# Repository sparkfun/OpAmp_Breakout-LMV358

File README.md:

SparkFun OpAmp Breakout - LMV358
========================================

[*SparkFun OpAmp Breakout - LMV358 (BOB-09816)*](https://www.sparkfun.com/products/9816)

 This is a simple Op Amp breakout board, set up as a 2-stage amplifier with a gain of 100 (gain of 10 for each stage). 
 The on-board trim pot sets the signal level between the stages, not the feedback path. 
 The bandwidth is set to 15.9kHz by a pair of feedback capacitors, or over 100kHz with the caps removed. 
 The LMV358 opamp can source up to 160mA and works well as a low impedance driver/buffer.

Repository Contents
-------------------

* **/Hardware** - Eagle design files (.brd, .sch)
* **/Production** - Production panel files (.brd)

Documentation
--------------

* **[SparkFun Fritzing repo](https://github.com/sparkfun/Fritzing_Parts)** - Fritzing diagrams for SparkFun products.
* **[SparkFun 3D Model repo](https://github.com/sparkfun/3D_Models)** - 3D models of SparkFun products. 

License Information
-------------------
This product is _**open source**_! 

The **hardware** is released under [Creative Commons ShareAlike 4.0 International](https://creativecommons.org/licenses/by-sa/4.0/).

Please use, reuse, and modify these files as you see fit. Please maintain attribution to SparkFun Electronics and release anything derivative under the same license.

Distributed as-is; no warranty is given.

- Your friends at SparkFun.

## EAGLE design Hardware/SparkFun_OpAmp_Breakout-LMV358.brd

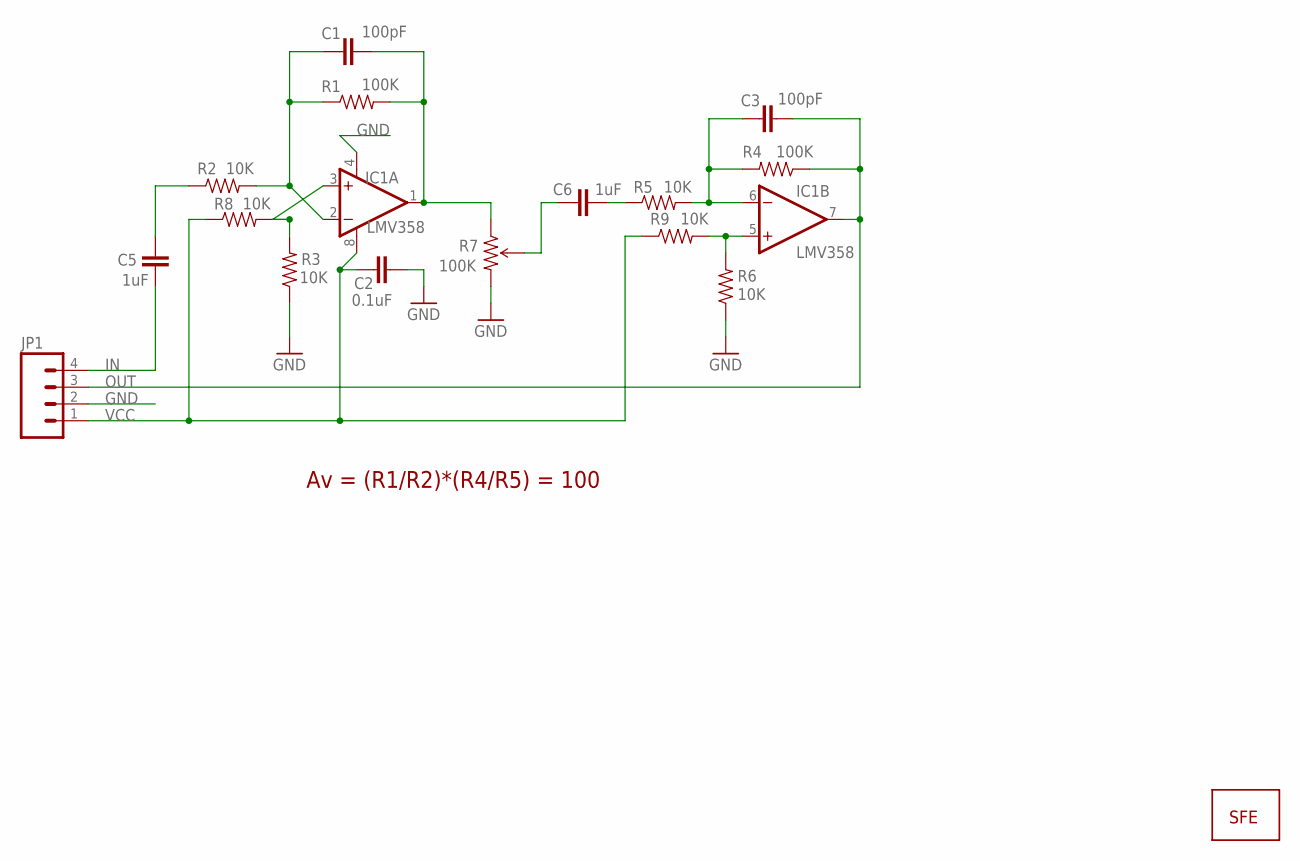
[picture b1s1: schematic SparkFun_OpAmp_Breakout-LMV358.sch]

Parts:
C1, C3: 100pF; 0402-CAP
C2: 0.1uF; 0402-CAP
C5, C6: 1uF; 0402-CAP
IC1: LMV358; SO08
JP1: M04PTH; 1X04
R1, R4: 100K; 0402-RES
R2, R3, R5, R6: 10K; 0402-RES
R7: 100K; TRIMPOT-3MM
R8, R9: 10K; C0402
U$3: LOGO-SFENEW; SFE-NEW-WEBLOGO

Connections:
GND: C2.2, IC1.4 (V-), JP1.2, R3.1, R6.1, R7.3 (CW)
IN: C5.1, JP1.4
IN1: C5.2, R2.1
unnamed: IC1.5 (+IN), R6.2, R9.2
unnamed: C1.1, IC1.2 (-IN), R1.1, R2.2
unnamed: IC1.3 (+IN), R3.2, R8.2
unnamed: C6.1, R5.1
unnamed: C6.2, R7.2 (WIPER)
unnamed: C3.1, IC1.6 (-IN), R4.2, R5.2
OUT: C3.2, IC1.7 (OUT), JP1.3, R4.1
OUT1: C1.2, IC1.1 (OUT), R1.2, R7.1 (CCW)
VCC: C2.1, IC1.8 (V+), JP1.1, R8.1, R9.1

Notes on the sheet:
Av = (R1/R2)*(R4/R5) = 100

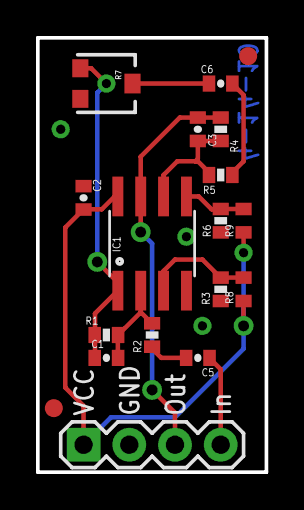
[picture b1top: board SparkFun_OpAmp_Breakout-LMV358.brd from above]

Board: 2 copper layers, 12.7 x 24.1 mm, 19 parts (1 on the bottom side), 12 nets.

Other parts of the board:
E$1, E$2: FIDUCIAL-1X2

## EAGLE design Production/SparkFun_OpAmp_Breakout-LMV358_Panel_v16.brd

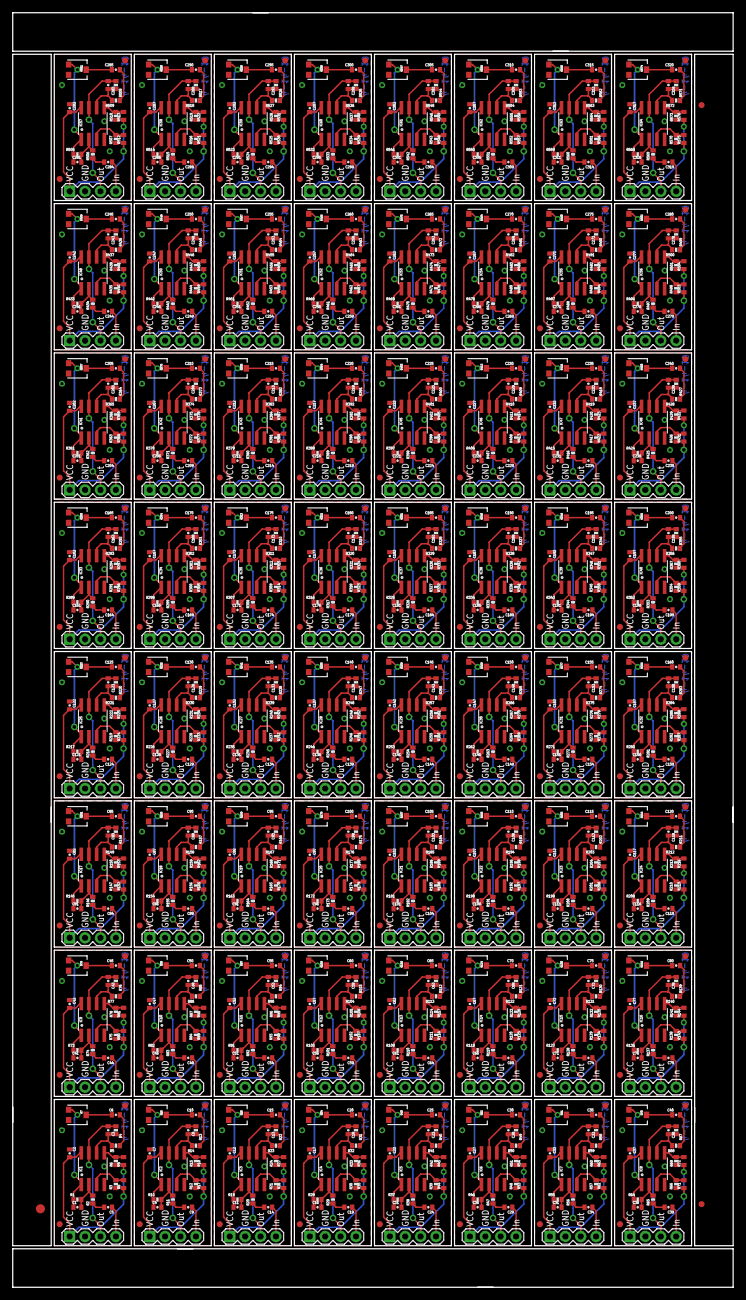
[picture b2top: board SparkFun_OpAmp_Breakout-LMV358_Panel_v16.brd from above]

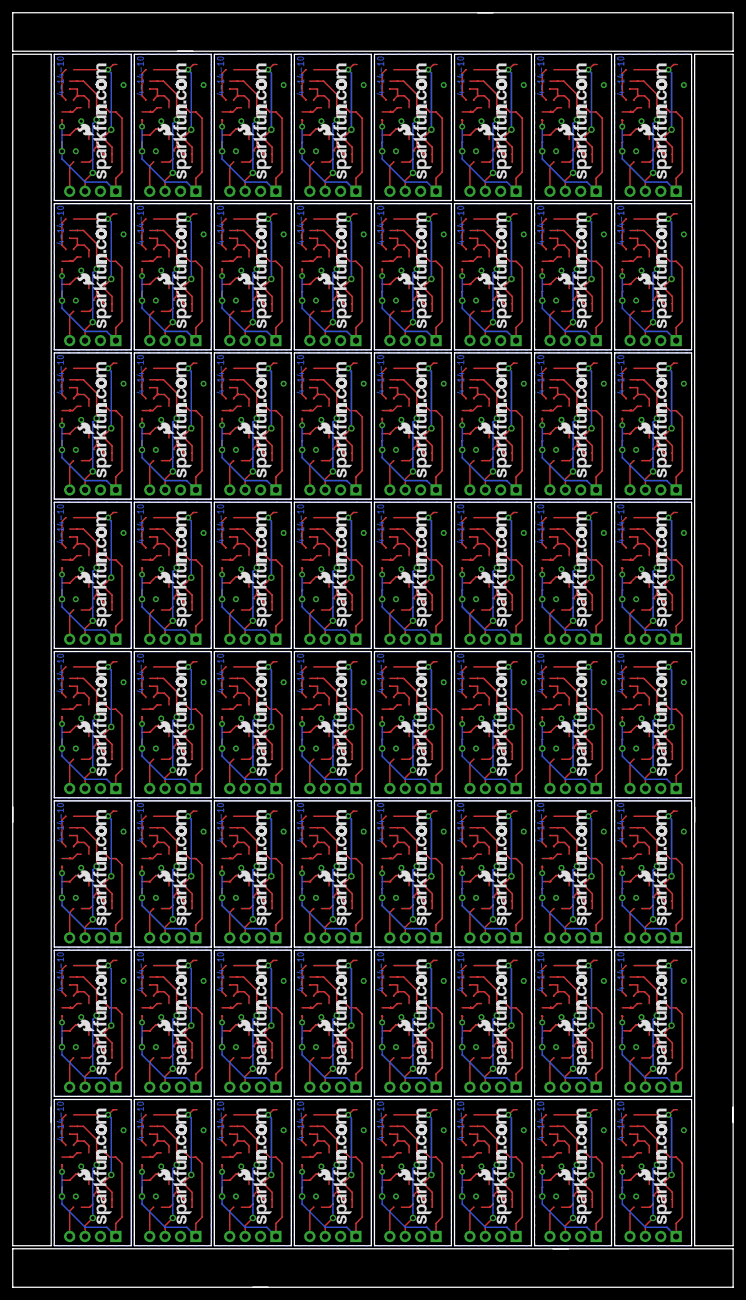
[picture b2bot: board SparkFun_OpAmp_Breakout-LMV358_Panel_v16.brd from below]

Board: 2 copper layers, 118.9 x 210.3 mm, 1219 parts (64 on the bottom side), 768 nets.

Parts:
C1, C3, C4, C8, C11, C13, C16, C18, C21, C23, C26, C28, C31, C33, C36, C38, C41, C43, C46, C48, C51, C53, C56, C58, C61, C63, C66, C68, C71, C73, C76, C78, C81, C83, C86, C88, C91, C93, C96, C98, C101, C103, C106, C108, C111, C113, C116, C118, C121, C123, C126, C128, C131, C133, C136, C138, C141, C143, C146, C148, C151, C153, C156, C158, C161, C163, C166, C168, C171, C173, C176, C178, C181, C183, C186, C188, C191, C193, C196, C198, C201, C203, C206, C208, C211, C213, C216, C218, C221, C223, C226, C228, C231, C233, C236, C238, C241, C243, C246, C248, C251, C253, C256, C258, C261, C263, C266, C268, C271, C273, C276, C278, C281, C283, C286, C288, C291, C293, C296, C298, C301, C303, C306, C308, C311, C313, C316, C318: 100pF; 0402-CAP
C2, C7, C12, C17, C22, C27, C32, C37, C42, C47, C52, C57, C62, C67, C72, C77, C82, C87, C92, C97, C102, C107, C112, C117, C122, C127, C132, C137, C142, C147, C152, C157, C162, C167, C172, C177, C182, C187, C192, C197, C202, C207, C212, C217, C222, C227, C232, C237, C242, C247, C252, C257, C262, C267, C272, C277, C282, C287, C292, C297, C302, C307, C312, C317: 0.1uF; 0402-CAP
C5, C6, C9, C10, C14, C15, C19, C20, C24, C25, C29, C30, C34, C35, C39, C40, C44, C45, C49, C50, C54, C55, C59, C60, C64, C65, C69, C70, C74, C75, C79, C80, C84, C85, C89, C90, C94, C95, C99, C100, C104, C105, C109, C110, C114, C115, C119, C120, C124, C125, C129, C130, C134, C135, C139, C140, C144, C145, C149, C150, C154, C155, C159, C160, C164, C165, C169, C170, C174, C175, C179, C180, C184, C185, C189, C190, C194, C195, C199, C200, C204, C205, C209, C210, C214, C215, C219, C220, C224, C225, C229, C230, C234, C235, C239, C240, C244, C245, C249, C250, C254, C255, C259, C260, C264, C265, C269, C270, C274, C275, C279, C280, C284, C285, C289, C290, C294, C295, C299, C300, C304, C305, C309, C310, C314, C315, C319, C320: 1uF; 0402-CAP
E$1, E$2, E$3, E$4, E$5, E$6, E$7, E$8, E$9, E$10, E$11, E$12, E$13, E$14, E$15, E$16, E$17, E$18, E$19, E$20, E$21, E$22, E$23, E$24, E$25, E$26, E$27, E$28, E$29, E$30, E$31, E$32, E$33, E$34, E$35, E$36, E$37, E$38, E$39, E$40, E$41, E$42, E$43, E$44, E$45, E$46, E$47, E$48, E$49, E$50, E$51, E$52, E$53, E$54, E$55, E$56, E$57, E$58, E$59, E$60, E$61, E$62, E$63, E$64, E$65, E$66, E$67, E$68, E$69, E$70, E$71, E$72, E$73, E$74, E$75, E$76, E$77, E$78, E$79, E$80, E$81, E$82, E$83, E$84, E$85, E$86, E$87, E$88, E$89, E$90, E$91, E$92, E$93, E$94, E$95, E$96, E$97, E$98, E$99, E$100, E$101, E$102, E$103, E$104, E$105, E$106, E$107, E$108, E$109, E$110, E$111, E$112, E$113, E$114, E$115, E$116, E$117, E$118, E$119, E$120, E$121, E$122, E$123, E$124, E$125, E$126, E$127, E$128, E$133, E$134: FIDUCIAL-1X2
E$129: FIDUCIAL-1.5X3
IC1, IC2, IC3, IC4, IC5, IC6, IC7, IC8, IC9, IC10, IC11, IC12, IC13, IC14, IC15, IC16, IC17, IC18, IC19, IC20, IC21, IC22, IC23, IC24, IC25, IC26, IC27, IC28, IC29, IC30, IC31, IC32, IC33, IC34, IC35, IC36, IC37, IC38, IC39, IC40, IC41, IC42, IC43, IC44, IC45, IC46, IC47, IC48, IC49, IC50, IC51, IC52, IC53, IC54, IC55, IC56, IC57, IC58, IC59, IC60, IC61, IC62, IC63, IC64: LMV358; SO08
JP1, JP2, JP3, JP4, JP5, JP6, JP7, JP8, JP9, JP10, JP11, JP12, JP13, JP14, JP15, JP16, JP17, JP18, JP19, JP20, JP21, JP22, JP23, JP24, JP25, JP26, JP27, JP28, JP29, JP30, JP31, JP32, JP33, JP34, JP35, JP36, JP37, JP38, JP39, JP40, JP41, JP42, JP43, JP44, JP45, JP46, JP47, JP48, JP49, JP50, JP51, JP52, JP53, JP54, JP55, JP56, JP57, JP58, JP59, JP60, JP61, JP62, JP63, JP64: 1X04
R1, R4, R10, R13, R19, R22, R28, R31, R37, R40, R46, R49, R55, R58, R64, R67, R73, R76, R82, R85, R91, R94, R100, R103, R109, R112, R118, R121, R127, R130, R136, R139, R145, R148, R154, R157, R163, R166, R172, R175, R181, R184, R190, R193, R199, R202, R208, R211, R217, R220, R226, R229, R235, R238, R244, R247, R253, R256, R262, R265, R271, R274, R280, R283, R289, R292, R298, R301, R307, R310, R316, R319, R325, R328, R334, R337, R343, R346, R352, R355, R361, R364, R370, R373, R379, R382, R388, R391, R397, R400, R406, R409, R415, R418, R424, R427, R433, R436, R442, R445, R451, R454, R460, R463, R469, R472, R478, R481, R487, R490, R496, R499, R505, R508, R514, R517, R523, R526, R532, R535, R541, R544, R550, R553, R559, R562, R568, R571: 100K; 0402-RES
R2, R3, R5, R6, R11, R12, R14, R15, R20, R21, R23, R24, R29, R30, R32, R33, R38, R39, R41, R42, R47, R48, R50, R51, R56, R57, R59, R60, R65, R66, R68, R69, R74, R75, R77, R78, R83, R84, R86, R87, R92, R93, R95, R96, R101, R102, R104, R105, R110, R111, R113, R114, R119, R120, R122, R123, R128, R129, R131, R132, R137, R138, R140, R141, R146, R147, R149, R150, R155, R156, R158, R159, R164, R165, R167, R168, R173, R174, R176, R177, R182, R183, R185, R186, R191, R192, R194, R195, R200, R201, R203, R204, R209, R210, R212, R213, R218, R219, R221, R222, R227, R228, R230, R231, R236, R237, R239, R240, R245, R246, R248, R249, R254, R255, R257, R258, R263, R264, R266, R267, R272, R273, R275, R276, R281, R282, R284, R285, R290, R291, R293, R294, R299, R300, R302, R303, R308, R309, R311, R312, R317, R318, R320, R321, R326, R327, R329, R330, R335, R336, R338, R339, R344, R345, R347, R348, R353, R354, R356, R357, R362, R363, R365, R366, R371, R372, R374, R375, R380, R381, R383, R384, R389, R390, R392, R393, R398, R399, R401, R402, R407, R408, R410, R411, R416, R417, R419, R420, R425, R426, R428, R429, R434, R435, R437, R438, R443, R444, R446, R447, R452, R453, R455, R456, R461, R462, R464, R465, R470, R471, R473, R474, R479, R480, R482, R483, R488, R489, R491, R492, R497, R498, R500, R501, R506, R507, R509, R510, R515, R516, R518, R519, R524, R525, R527, R528, R533, R534, R536, R537, R542, R543, R545, R546, R551, R552, R554, R555, R560, R561, R563, R564, R569, R570, R572, R573: 10K; 0402-RES
R7, R16, R25, R34, R43, R52, R61, R70, R79, R88, R97, R106, R115, R124, R133, R142, R151, R160, R169, R178, R187, R196, R205, R214, R223, R232, R241, R250, R259, R268, R277, R286, R295, R304, R313, R322, R331, R340, R349, R358, R367, R376, R385, R394, R403, R412, R421, R430, R439, R448, R457, R466, R475, R484, R493, R502, R511, R520, R529, R538, R547, R556, R565, R574: 100K; TRIMPOT-3MM
R8, R9, R17, R18, R26, R27, R35, R36, R44, R45, R53, R54, R62, R63, R71, R72, R80, R81, R89, R90, R98, R99, R107, R108, R116, R117, R125, R126, R134, R135, R143, R144, R152, R153, R161, R162, R170, R171, R179, R180, R188, R189, R197, R198, R206, R207, R215, R216, R224, R225, R233, R234, R242, R243, R251, R252, R260, R261, R269, R270, R278, R279, R287, R288, R296, R297, R305, R306, R314, R315, R323, R324, R332, R333, R341, R342, R350, R351, R359, R360, R368, R369, R377, R378, R386, R387, R395, R396, R404, R405, R413, R414, R422, R423, R431, R432, R440, R441, R449, R450, R458, R459, R467, R468, R476, R477, R485, R486, R494, R495, R503, R504, R512, R513, R521, R522, R530, R531, R539, R540, R548, R549, R557, R558, R566, R567, R575, R576: 10K; C0402
U$1, U$2, U$3, U$4, U$5, U$6, U$7, U$8, U$9, U$10, U$11, U$12, U$13, U$14, U$15, U$16, U$17, U$18, U$19, U$20, U$21, U$22, U$23, U$24, U$25, U$26, U$27, U$28, U$29, U$30, U$31, U$32, U$33, U$34, U$35, U$36, U$37, U$38, U$39, U$40, U$41, U$42, U$43, U$44, U$45, U$46, U$47, U$48, U$49, U$50, U$51, U$52, U$53, U$54, U$55, U$56, U$57, U$58, U$59, U$60, U$61, U$62, U$63, U$64: LOGO-SFENEW; SFE-NEW-WEBLOGO

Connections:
GND: C2.2, IC1.4, JP1.2, R3.1, R6.1, R7.3
GND1: C7.2, IC2.4, JP2.2, R12.1, R15.1, R16.3
GND2: C12.2, IC3.4, JP3.2, R21.1, R24.1, R25.3
GND3: C17.2, IC4.4, JP4.2, R30.1, R33.1, R34.3
GND4: C22.2, IC5.4, JP5.2, R39.1, R42.1, R43.3
GND5: C27.2, IC6.4, JP6.2, R48.1, R51.1, R52.3
GND6: C32.2, IC7.4, JP7.2, R57.1, R60.1, R61.3
GND7: C37.2, IC8.4, JP8.2, R66.1, R69.1, R70.3
GND8: C42.2, IC9.4, JP9.2, R75.1, R78.1, R79.3
GND9: C47.2, IC10.4, JP10.2, R84.1, R87.1, R88.3
GND10: C52.2, IC11.4, JP11.2, R93.1, R96.1, R97.3
GND11: C57.2, IC12.4, JP12.2, R102.1, R105.1, R106.3
GND12: C62.2, IC13.4, JP13.2, R111.1, R114.1, R115.3
GND13: C67.2, IC14.4, JP14.2, R120.1, R123.1, R124.3
GND14: C72.2, IC15.4, JP15.2, R129.1, R132.1, R133.3
GND15: C77.2, IC16.4, JP16.2, R138.1, R141.1, R142.3
GND16: C82.2, IC17.4, JP17.2, R147.1, R150.1, R151.3
GND17: C87.2, IC18.4, JP18.2, R156.1, R159.1, R160.3
GND18: C92.2, IC19.4, JP19.2, R165.1, R168.1, R169.3
GND19: C97.2, IC20.4, JP20.2, R174.1, R177.1, R178.3
GND20: C102.2, IC21.4, JP21.2, R183.1, R186.1, R187.3
GND21: C107.2, IC22.4, JP22.2, R192.1, R195.1, R196.3
GND22: C112.2, IC23.4, JP23.2, R201.1, R204.1, R205.3
GND23: C117.2, IC24.4, JP24.2, R210.1, R213.1, R214.3
GND24: C122.2, IC25.4, JP25.2, R219.1, R222.1, R223.3
GND25: C127.2, IC26.4, JP26.2, R228.1, R231.1, R232.3
GND26: C132.2, IC27.4, JP27.2, R237.1, R240.1, R241.3
GND27: C137.2, IC28.4, JP28.2, R246.1, R249.1, R250.3
GND28: C142.2, IC29.4, JP29.2, R255.1, R258.1, R259.3
GND29: C147.2, IC30.4, JP30.2, R264.1, R267.1, R268.3
GND30: C152.2, IC31.4, JP31.2, R273.1, R276.1, R277.3
GND31: C157.2, IC32.4, JP32.2, R282.1, R285.1, R286.3
GND32: C162.2, IC33.4, JP33.2, R291.1, R294.1, R295.3
GND33: C167.2, IC34.4, JP34.2, R300.1, R303.1, R304.3
GND34: C172.2, IC35.4, JP35.2, R309.1, R312.1, R313.3
GND35: C177.2, IC36.4, JP36.2, R318.1, R321.1, R322.3
GND36: C182.2, IC37.4, JP37.2, R327.1, R330.1, R331.3
GND37: C187.2, IC38.4, JP38.2, R336.1, R339.1, R340.3
GND38: C192.2, IC39.4, JP39.2, R345.1, R348.1, R349.3
GND39: C197.2, IC40.4, JP40.2, R354.1, R357.1, R358.3
GND40: C202.2, IC41.4, JP41.2, R363.1, R366.1, R367.3
GND41: C207.2, IC42.4, JP42.2, R372.1, R375.1, R376.3
GND42: C212.2, IC43.4, JP43.2, R381.1, R384.1, R385.3
GND43: C217.2, IC44.4, JP44.2, R390.1, R393.1, R394.3
GND44: C222.2, IC45.4, JP45.2, R399.1, R402.1, R403.3
GND45: C227.2, IC46.4, JP46.2, R408.1, R411.1, R412.3
GND46: C232.2, IC47.4, JP47.2, R417.1, R420.1, R421.3
GND47: C237.2, IC48.4, JP48.2, R426.1, R429.1, R430.3
GND48: C242.2, IC49.4, JP49.2, R435.1, R438.1, R439.3
GND49: C247.2, IC50.4, JP50.2, R444.1, R447.1, R448.3
GND50: C252.2, IC51.4, JP51.2, R453.1, R456.1, R457.3
GND51: C257.2, IC52.4, JP52.2, R462.1, R465.1, R466.3
GND52: C262.2, IC53.4, JP53.2, R471.1, R474.1, R475.3
GND53: C267.2, IC54.4, JP54.2, R480.1, R483.1, R484.3
GND54: C272.2, IC55.4, JP55.2, R489.1, R492.1, R493.3
GND55: C277.2, IC56.4, JP56.2, R498.1, R501.1, R502.3
GND56: C282.2, IC57.4, JP57.2, R507.1, R510.1, R511.3
GND57: C287.2, IC58.4, JP58.2, R516.1, R519.1, R520.3
GND58: C292.2, IC59.4, JP59.2, R525.1, R528.1, R529.3
GND59: C297.2, IC60.4, JP60.2, R534.1, R537.1, R538.3
GND60: C302.2, IC61.4, JP61.2, R543.1, R546.1, R547.3
GND61: C307.2, IC62.4, JP62.2, R552.1, R555.1, R556.3
GND62: C312.2, IC63.4, JP63.2, R561.1, R564.1, R565.3
GND63: C317.2, IC64.4, JP64.2, R570.1, R573.1, R574.3
IN: C5.1, JP1.4
IN1: C5.2, R2.1
IN2: C9.2, R11.1
IN3: C9.1, JP2.4
IN4: C14.2, R20.1
IN5: C14.1, JP3.4
IN6: C19.2, R29.1
IN7: C19.1, JP4.4
IN8: C24.2, R38.1
IN9: C24.1, JP5.4
IN10: C29.2, R47.1
IN11: C29.1, JP6.4
IN12: C34.2, R56.1
IN13: C34.1, JP7.4
IN14: C39.2, R65.1
IN15: C39.1, JP8.4
IN16: C44.2, R74.1
IN17: C44.1, JP9.4
IN18: C49.2, R83.1
IN19: C49.1, JP10.4
IN20: C54.2, R92.1
IN21: C54.1, JP11.4
IN22: C59.2, R101.1
IN23: C59.1, JP12.4
IN24: C64.2, R110.1
IN25: C64.1, JP13.4
IN26: C69.2, R119.1
IN27: C69.1, JP14.4
IN28: C74.2, R128.1
IN29: C74.1, JP15.4
IN30: C79.2, R137.1
IN31: C79.1, JP16.4
IN32: C84.2, R146.1
IN33: C84.1, JP17.4
IN34: C89.2, R155.1
IN35: C89.1, JP18.4
IN36: C94.2, R164.1
IN37: C94.1, JP19.4
IN38: C99.2, R173.1
IN39: C99.1, JP20.4
IN40: C104.2, R182.1
IN41: C104.1, JP21.4
IN42: C109.2, R191.1
IN43: C109.1, JP22.4
IN44: C114.2, R200.1
IN45: C114.1, JP23.4
IN46: C119.2, R209.1
IN47: C119.1, JP24.4
IN48: C124.2, R218.1
IN49: C124.1, JP25.4
IN50: C129.2, R227.1
IN51: C129.1, JP26.4
IN52: C134.2, R236.1
IN53: C134.1, JP27.4
IN54: C139.2, R245.1
IN55: C139.1, JP28.4
IN56: C144.2, R254.1
IN57: C144.1, JP29.4
IN58: C149.2, R263.1
IN59: C149.1, JP30.4
IN60: C154.2, R272.1
IN61: C154.1, JP31.4
IN62: C159.2, R281.1
IN63: C159.1, JP32.4
IN64: C164.2, R290.1
IN65: C164.1, JP33.4
IN66: C169.2, R299.1
IN67: C169.1, JP34.4
IN68: C174.2, R308.1
IN69: C174.1, JP35.4
IN70: C179.2, R317.1
IN71: C179.1, JP36.4
IN72: C184.2, R326.1
IN73: C184.1, JP37.4
IN74: C189.2, R335.1
IN75: C189.1, JP38.4
IN76: C194.2, R344.1
IN77: C194.1, JP39.4
IN78: C199.2, R353.1
IN79: C199.1, JP40.4
IN80: C204.2, R362.1
IN81: C204.1, JP41.4
IN82: C209.2, R371.1
IN83: C209.1, JP42.4
IN84: C214.2, R380.1
IN85: C214.1, JP43.4
IN86: C219.2, R389.1
IN87: C219.1, JP44.4
IN88: C224.2, R398.1
IN89: C224.1, JP45.4
IN90: C229.2, R407.1
IN91: C229.1, JP46.4
IN92: C234.2, R416.1
IN93: C234.1, JP47.4
IN94: C239.2, R425.1
IN95: C239.1, JP48.4
IN96: C244.2, R434.1
IN97: C244.1, JP49.4
IN98: C249.2, R443.1
IN99: C249.1, JP50.4
IN100: C254.2, R452.1
IN101: C254.1, JP51.4
IN102: C259.2, R461.1
IN103: C259.1, JP52.4
IN104: C264.2, R470.1
IN105: C264.1, JP53.4
IN106: C269.2, R479.1
IN107: C269.1, JP54.4
IN108: C274.2, R488.1
IN109: C274.1, JP55.4
IN110: C279.2, R497.1
IN111: C279.1, JP56.4
IN112: C284.2, R506.1
IN113: C284.1, JP57.4
IN114: C289.2, R515.1
IN115: C289.1, JP58.4
IN116: C294.2, R524.1
IN117: C294.1, JP59.4
IN118: C299.2, R533.1
IN119: C299.1, JP60.4
IN120: C304.2, R542.1
IN121: C304.1, JP61.4
IN122: C309.2, R551.1
IN123: C309.1, JP62.4
IN124: C314.2, R560.1
IN125: C314.1, JP63.4
IN126: C319.2, R569.1
IN127: C319.1, JP64.4
unnamed: IC1.5, R6.2, R9.2
unnamed: C1.1, IC1.2, R1.1, R2.2
unnamed: IC1.3, R3.2, R8.2
unnamed: C6.1, R5.1
unnamed: C6.2, R7.2
unnamed: C4.1, IC2.2, R10.1, R11.2
unnamed: C3.1, IC1.6, R4.2, R5.2
unnamed: C8.1, IC2.6, R13.2, R14.2
unnamed: C10.1, R14.1
unnamed: C10.2, R16.2
unnamed: IC2.5, R15.2, R18.2
unnamed: IC2.3, R12.2, R17.2
unnamed: C11.1, IC3.2, R19.1, R20.2
unnamed: C13.1, IC3.6, R22.2, R23.2
unnamed: C15.1, R23.1
unnamed: C15.2, R25.2
unnamed: IC3.5, R24.2, R27.2
unnamed: IC3.3, R21.2, R26.2
unnamed: C16.1, IC4.2, R28.1, R29.2
unnamed: C18.1, IC4.6, R31.2, R32.2
unnamed: C20.1, R32.1
unnamed: C20.2, R34.2
unnamed: IC4.5, R33.2, R36.2
unnamed: IC4.3, R30.2, R35.2
unnamed: C21.1, IC5.2, R37.1, R38.2
unnamed: C23.1, IC5.6, R40.2, R41.2
unnamed: C25.1, R41.1
unnamed: C25.2, R43.2
unnamed: IC5.5, R42.2, R45.2
unnamed: IC5.3, R39.2, R44.2
unnamed: C26.1, IC6.2, R46.1, R47.2
unnamed: C28.1, IC6.6, R49.2, R50.2
unnamed: C30.1, R50.1
unnamed: C30.2, R52.2
unnamed: IC6.5, R51.2, R54.2
unnamed: IC6.3, R48.2, R53.2
unnamed: C31.1, IC7.2, R55.1, R56.2
unnamed: C33.1, IC7.6, R58.2, R59.2
unnamed: C35.1, R59.1
unnamed: C35.2, R61.2
unnamed: IC7.5, R60.2, R63.2
unnamed: IC7.3, R57.2, R62.2
unnamed: C36.1, IC8.2, R64.1, R65.2
unnamed: C38.1, IC8.6, R67.2, R68.2
unnamed: C40.1, R68.1
unnamed: C40.2, R70.2
unnamed: IC8.5, R69.2, R72.2
unnamed: IC8.3, R66.2, R71.2
unnamed: C41.1, IC9.2, R73.1, R74.2
unnamed: C43.1, IC9.6, R76.2, R77.2
unnamed: C45.1, R77.1
unnamed: C45.2, R79.2
unnamed: IC9.5, R78.2, R81.2
unnamed: IC9.3, R75.2, R80.2
unnamed: C46.1, IC10.2, R82.1, R83.2
unnamed: C48.1, IC10.6, R85.2, R86.2
unnamed: C50.1, R86.1
unnamed: C50.2, R88.2
unnamed: IC10.5, R87.2, R90.2
unnamed: IC10.3, R84.2, R89.2
unnamed: C51.1, IC11.2, R91.1, R92.2
unnamed: C53.1, IC11.6, R94.2, R95.2
unnamed: C55.1, R95.1
unnamed: C55.2, R97.2
unnamed: IC11.5, R96.2, R99.2
unnamed: IC11.3, R93.2, R98.2
unnamed: C56.1, IC12.2, R100.1, R101.2
unnamed: C58.1, IC12.6, R103.2, R104.2
unnamed: C60.1, R104.1
unnamed: C60.2, R106.2
unnamed: IC12.5, R105.2, R108.2
unnamed: IC12.3, R102.2, R107.2
unnamed: C61.1, IC13.2, R109.1, R110.2
unnamed: C63.1, IC13.6, R112.2, R113.2
unnamed: C65.1, R113.1
unnamed: C65.2, R115.2
unnamed: IC13.5, R114.2, R117.2
unnamed: IC13.3, R111.2, R116.2
unnamed: C66.1, IC14.2, R118.1, R119.2
unnamed: C68.1, IC14.6, R121.2, R122.2
unnamed: C70.1, R122.1
unnamed: C70.2, R124.2
unnamed: IC14.5, R123.2, R126.2
unnamed: IC14.3, R120.2, R125.2
unnamed: C71.1, IC15.2, R127.1, R128.2
unnamed: C73.1, IC15.6, R130.2, R131.2
unnamed: C75.1, R131.1
unnamed: C75.2, R133.2
unnamed: IC15.5, R132.2, R135.2
unnamed: IC15.3, R129.2, R134.2
unnamed: C76.1, IC16.2, R136.1, R137.2
unnamed: C78.1, IC16.6, R139.2, R140.2
unnamed: C80.1, R140.1
unnamed: C80.2, R142.2
unnamed: IC16.5, R141.2, R144.2
unnamed: IC16.3, R138.2, R143.2
unnamed: C81.1, IC17.2, R145.1, R146.2
unnamed: C83.1, IC17.6, R148.2, R149.2
unnamed: C85.1, R149.1
unnamed: C85.2, R151.2
unnamed: IC17.5, R150.2, R153.2
unnamed: IC17.3, R147.2, R152.2
unnamed: C86.1, IC18.2, R154.1, R155.2
unnamed: C88.1, IC18.6, R157.2, R158.2
unnamed: C90.1, R158.1
unnamed: C90.2, R160.2
unnamed: IC18.5, R159.2, R162.2
unnamed: IC18.3, R156.2, R161.2
unnamed: C91.1, IC19.2, R163.1, R164.2
unnamed: C93.1, IC19.6, R166.2, R167.2
unnamed: C95.1, R167.1
unnamed: C95.2, R169.2
unnamed: IC19.5, R168.2, R171.2
unnamed: IC19.3, R165.2, R170.2
unnamed: C96.1, IC20.2, R172.1, R173.2
unnamed: C98.1, IC20.6, R175.2, R176.2
unnamed: C100.1, R176.1
unnamed: C100.2, R178.2
unnamed: IC20.5, R177.2, R180.2
unnamed: IC20.3, R174.2, R179.2
unnamed: C101.1, IC21.2, R181.1, R182.2
unnamed: C103.1, IC21.6, R184.2, R185.2
unnamed: C105.1, R185.1
unnamed: C105.2, R187.2
unnamed: IC21.5, R186.2, R189.2
unnamed: IC21.3, R183.2, R188.2
unnamed: C106.1, IC22.2, R190.1, R191.2
unnamed: C108.1, IC22.6, R193.2, R194.2
unnamed: C110.1, R194.1
unnamed: C110.2, R196.2
unnamed: IC22.5, R195.2, R198.2
unnamed: IC22.3, R192.2, R197.2
unnamed: C111.1, IC23.2, R199.1, R200.2
unnamed: C113.1, IC23.6, R202.2, R203.2
unnamed: C115.1, R203.1
unnamed: C115.2, R205.2
unnamed: IC23.5, R204.2, R207.2
unnamed: IC23.3, R201.2, R206.2
unnamed: C116.1, IC24.2, R208.1, R209.2
unnamed: C118.1, IC24.6, R211.2, R212.2
unnamed: C120.1, R212.1
unnamed: C120.2, R214.2
unnamed: IC24.5, R213.2, R216.2
unnamed: IC24.3, R210.2, R215.2
unnamed: C121.1, IC25.2, R217.1, R218.2
unnamed: C123.1, IC25.6, R220.2, R221.2
unnamed: C125.1, R221.1
unnamed: C125.2, R223.2
unnamed: IC25.5, R222.2, R225.2
unnamed: IC25.3, R219.2, R224.2
unnamed: C126.1, IC26.2, R226.1, R227.2
unnamed: C128.1, IC26.6, R229.2, R230.2
unnamed: C130.1, R230.1
unnamed: C130.2, R232.2
unnamed: IC26.5, R231.2, R234.2
unnamed: IC26.3, R228.2, R233.2
unnamed: C131.1, IC27.2, R235.1, R236.2
unnamed: C133.1, IC27.6, R238.2, R239.2
unnamed: C135.1, R239.1
unnamed: C135.2, R241.2
unnamed: IC27.5, R240.2, R243.2
unnamed: IC27.3, R237.2, R242.2
unnamed: C136.1, IC28.2, R244.1, R245.2
unnamed: C138.1, IC28.6, R247.2, R248.2
unnamed: C140.1, R248.1
unnamed: C140.2, R250.2
unnamed: IC28.5, R249.2, R252.2
unnamed: IC28.3, R246.2, R251.2
unnamed: C141.1, IC29.2, R253.1, R254.2
unnamed: C143.1, IC29.6, R256.2, R257.2
unnamed: C145.1, R257.1
unnamed: C145.2, R259.2
unnamed: IC29.5, R258.2, R261.2
unnamed: IC29.3, R255.2, R260.2
unnamed: C146.1, IC30.2, R262.1, R263.2
unnamed: C148.1, IC30.6, R265.2, R266.2
unnamed: C150.1, R266.1
unnamed: C150.2, R268.2
unnamed: IC30.5, R267.2, R270.2
unnamed: IC30.3, R264.2, R269.2
unnamed: C151.1, IC31.2, R271.1, R272.2
unnamed: C153.1, IC31.6, R274.2, R275.2
unnamed: C155.1, R275.1
unnamed: C155.2, R277.2
unnamed: IC31.5, R276.2, R279.2
unnamed: IC31.3, R273.2, R278.2
unnamed: C156.1, IC32.2, R280.1, R281.2
unnamed: C158.1, IC32.6, R283.2, R284.2
unnamed: C160.1, R284.1
unnamed: C160.2, R286.2
unnamed: IC32.5, R285.2, R288.2
unnamed: IC32.3, R282.2, R287.2
unnamed: C161.1, IC33.2, R289.1, R290.2
unnamed: C163.1, IC33.6, R292.2, R293.2
unnamed: C165.1, R293.1
unnamed: C165.2, R295.2
unnamed: IC33.5, R294.2, R297.2
unnamed: IC33.3, R291.2, R296.2
unnamed: C166.1, IC34.2, R298.1, R299.2
unnamed: C168.1, IC34.6, R301.2, R302.2
unnamed: C170.1, R302.1
unnamed: C170.2, R304.2
unnamed: IC34.5, R303.2, R306.2
unnamed: IC34.3, R300.2, R305.2
unnamed: C171.1, IC35.2, R307.1, R308.2
unnamed: C173.1, IC35.6, R310.2, R311.2
unnamed: C175.1, R311.1
unnamed: C175.2, R313.2
unnamed: IC35.5, R312.2, R315.2
unnamed: IC35.3, R309.2, R314.2
unnamed: C176.1, IC36.2, R316.1, R317.2
unnamed: C178.1, IC36.6, R319.2, R320.2
unnamed: C180.1, R320.1
unnamed: C180.2, R322.2
unnamed: IC36.5, R321.2, R324.2
unnamed: IC36.3, R318.2, R323.2
unnamed: C181.1, IC37.2, R325.1, R326.2
unnamed: C183.1, IC37.6, R328.2, R329.2
unnamed: C185.1, R329.1
unnamed: C185.2, R331.2
unnamed: IC37.5, R330.2, R333.2
unnamed: IC37.3, R327.2, R332.2
unnamed: C186.1, IC38.2, R334.1, R335.2
unnamed: C188.1, IC38.6, R337.2, R338.2
unnamed: C190.1, R338.1
unnamed: C190.2, R340.2
unnamed: IC38.5, R339.2, R342.2
unnamed: IC38.3, R336.2, R341.2
unnamed: C191.1, IC39.2, R343.1, R344.2
unnamed: C193.1, IC39.6, R346.2, R347.2
unnamed: C195.1, R347.1
unnamed: C195.2, R349.2
unnamed: IC39.5, R348.2, R351.2
unnamed: IC39.3, R345.2, R350.2
unnamed: C196.1, IC40.2, R352.1, R353.2
unnamed: C198.1, IC40.6, R355.2, R356.2
unnamed: C200.1, R356.1
unnamed: C200.2, R358.2
unnamed: IC40.5, R357.2, R360.2
unnamed: IC40.3, R354.2, R359.2
unnamed: C201.1, IC41.2, R361.1, R362.2
unnamed: C203.1, IC41.6, R364.2, R365.2
unnamed: C205.1, R365.1
unnamed: C205.2, R367.2
unnamed: IC41.5, R366.2, R369.2
unnamed: IC41.3, R363.2, R368.2
unnamed: C206.1, IC42.2, R370.1, R371.2
unnamed: C208.1, IC42.6, R373.2, R374.2
unnamed: C210.1, R374.1
unnamed: C210.2, R376.2
unnamed: IC42.5, R375.2, R378.2
unnamed: IC42.3, R372.2, R377.2
unnamed: C211.1, IC43.2, R379.1, R380.2
unnamed: C213.1, IC43.6, R382.2, R383.2
unnamed: C215.1, R383.1
unnamed: C215.2, R385.2
unnamed: IC43.5, R384.2, R387.2
unnamed: IC43.3, R381.2, R386.2
unnamed: C216.1, IC44.2, R388.1, R389.2
unnamed: C218.1, IC44.6, R391.2, R392.2
unnamed: C220.1, R392.1
unnamed: C220.2, R394.2
unnamed: IC44.5, R393.2, R396.2
unnamed: IC44.3, R390.2, R395.2
unnamed: C221.1, IC45.2, R397.1, R398.2
unnamed: C223.1, IC45.6, R400.2, R401.2
unnamed: C225.1, R401.1
unnamed: C225.2, R403.2
unnamed: IC45.5, R402.2, R405.2
unnamed: IC45.3, R399.2, R404.2
unnamed: C226.1, IC46.2, R406.1, R407.2
unnamed: C228.1, IC46.6, R409.2, R410.2
unnamed: C230.1, R410.1
unnamed: C230.2, R412.2
unnamed: IC46.5, R411.2, R414.2
unnamed: IC46.3, R408.2, R413.2
unnamed: C231.1, IC47.2, R415.1, R416.2
unnamed: C233.1, IC47.6, R418.2, R419.2
unnamed: C235.1, R419.1
unnamed: C235.2, R421.2
unnamed: IC47.5, R420.2, R423.2
unnamed: IC47.3, R417.2, R422.2
unnamed: C236.1, IC48.2, R424.1, R425.2
unnamed: C238.1, IC48.6, R427.2, R428.2
unnamed: C240.1, R428.1
unnamed: C240.2, R430.2
unnamed: IC48.5, R429.2, R432.2
unnamed: IC48.3, R426.2, R431.2
unnamed: C241.1, IC49.2, R433.1, R434.2
unnamed: C243.1, IC49.6, R436.2, R437.2
unnamed: C245.1, R437.1
unnamed: C245.2, R439.2
unnamed: IC49.5, R438.2, R441.2
unnamed: IC49.3, R435.2, R440.2
unnamed: C246.1, IC50.2, R442.1, R443.2
unnamed: C248.1, IC50.6, R445.2, R446.2
unnamed: C250.1, R446.1
unnamed: C250.2, R448.2
unnamed: IC50.5, R447.2, R450.2
unnamed: IC50.3, R444.2, R449.2
unnamed: C251.1, IC51.2, R451.1, R452.2
unnamed: C253.1, IC51.6, R454.2, R455.2
unnamed: C255.1, R455.1
unnamed: C255.2, R457.2
unnamed: IC51.5, R456.2, R459.2
unnamed: IC51.3, R453.2, R458.2
unnamed: C256.1, IC52.2, R460.1, R461.2
unnamed: C258.1, IC52.6, R463.2, R464.2
unnamed: C260.1, R464.1
unnamed: C260.2, R466.2
unnamed: IC52.5, R465.2, R468.2
unnamed: IC52.3, R462.2, R467.2
unnamed: C261.1, IC53.2, R469.1, R470.2
unnamed: C263.1, IC53.6, R472.2, R473.2
unnamed: C265.1, R473.1
unnamed: C265.2, R475.2
unnamed: IC53.5, R474.2, R477.2
unnamed: IC53.3, R471.2, R476.2
unnamed: C266.1, IC54.2, R478.1, R479.2
unnamed: C268.1, IC54.6, R481.2, R482.2
unnamed: C270.1, R482.1
unnamed: C270.2, R484.2
unnamed: IC54.5, R483.2, R486.2
unnamed: IC54.3, R480.2, R485.2
unnamed: C271.1, IC55.2, R487.1, R488.2
unnamed: C273.1, IC55.6, R490.2, R491.2
unnamed: C275.1, R491.1
unnamed: C275.2, R493.2
unnamed: IC55.5, R492.2, R495.2
unnamed: IC55.3, R489.2, R494.2
unnamed: C276.1, IC56.2, R496.1, R497.2
unnamed: C278.1, IC56.6, R499.2, R500.2
unnamed: C280.1, R500.1
unnamed: C280.2, R502.2
unnamed: IC56.5, R501.2, R504.2
unnamed: IC56.3, R498.2, R503.2
unnamed: C281.1, IC57.2, R505.1, R506.2
unnamed: C283.1, IC57.6, R508.2, R509.2
unnamed: C285.1, R509.1
unnamed: C285.2, R511.2
unnamed: IC57.5, R510.2, R513.2
unnamed: IC57.3, R507.2, R512.2
unnamed: C286.1, IC58.2, R514.1, R515.2
unnamed: C288.1, IC58.6, R517.2, R518.2
unnamed: C290.1, R518.1
unnamed: C290.2, R520.2
unnamed: IC58.5, R519.2, R522.2
unnamed: IC58.3, R516.2, R521.2
unnamed: C291.1, IC59.2, R523.1, R524.2
unnamed: C293.1, IC59.6, R526.2, R527.2
unnamed: C295.1, R527.1
unnamed: C295.2, R529.2
unnamed: IC59.5, R528.2, R531.2
unnamed: IC59.3, R525.2, R530.2
unnamed: C296.1, IC60.2, R532.1, R533.2
unnamed: C298.1, IC60.6, R535.2, R536.2
unnamed: C300.1, R536.1
unnamed: C300.2, R538.2
unnamed: IC60.5, R537.2, R540.2
unnamed: IC60.3, R534.2, R539.2
unnamed: C301.1, IC61.2, R541.1, R542.2
unnamed: C303.1, IC61.6, R544.2, R545.2
unnamed: C305.1, R545.1
unnamed: C305.2, R547.2
unnamed: IC61.5, R546.2, R549.2
unnamed: IC61.3, R543.2, R548.2
unnamed: C306.1, IC62.2, R550.1, R551.2
unnamed: C308.1, IC62.6, R553.2, R554.2
unnamed: C310.1, R554.1
unnamed: C310.2, R556.2
unnamed: IC62.5, R555.2, R558.2
unnamed: IC62.3, R552.2, R557.2
unnamed: C311.1, IC63.2, R559.1, R560.2
unnamed: C313.1, IC63.6, R562.2, R563.2
unnamed: C315.1, R563.1
unnamed: C315.2, R565.2
unnamed: IC63.5, R564.2, R567.2
unnamed: IC63.3, R561.2, R566.2
unnamed: C316.1, IC64.2, R568.1, R569.2
unnamed: C318.1, IC64.6, R571.2, R572.2
unnamed: C320.1, R572.1
unnamed: C320.2, R574.2
unnamed: IC64.5, R573.2, R576.2
unnamed: IC64.3, R570.2, R575.2
OUT: C3.2, IC1.7, JP1.3, R4.1
OUT1: C1.2, IC1.1, R1.2, R7.1
OUT2: C4.2, IC2.1, R10.2, R16.1
OUT3: C8.2, IC2.7, JP2.3, R13.1
OUT4: C11.2, IC3.1, R19.2, R25.1
OUT5: C13.2, IC3.7, JP3.3, R22.1
OUT6: C16.2, IC4.1, R28.2, R34.1
OUT7: C18.2, IC4.7, JP4.3, R31.1
OUT8: C21.2, IC5.1, R37.2, R43.1
OUT9: C23.2, IC5.7, JP5.3, R40.1
OUT10: C26.2, IC6.1, R46.2, R52.1
OUT11: C28.2, IC6.7, JP6.3, R49.1
OUT12: C31.2, IC7.1, R55.2, R61.1
OUT13: C33.2, IC7.7, JP7.3, R58.1
OUT14: C36.2, IC8.1, R64.2, R70.1
OUT15: C38.2, IC8.7, JP8.3, R67.1
OUT16: C41.2, IC9.1, R73.2, R79.1
OUT17: C43.2, IC9.7, JP9.3, R76.1
OUT18: C46.2, IC10.1, R82.2, R88.1
OUT19: C48.2, IC10.7, JP10.3, R85.1
OUT20: C51.2, IC11.1, R91.2, R97.1
OUT21: C53.2, IC11.7, JP11.3, R94.1
OUT22: C56.2, IC12.1, R100.2, R106.1
OUT23: C58.2, IC12.7, JP12.3, R103.1
OUT24: C61.2, IC13.1, R109.2, R115.1
OUT25: C63.2, IC13.7, JP13.3, R112.1
OUT26: C66.2, IC14.1, R118.2, R124.1
OUT27: C68.2, IC14.7, JP14.3, R121.1
OUT28: C71.2, IC15.1, R127.2, R133.1
OUT29: C73.2, IC15.7, JP15.3, R130.1
OUT30: C76.2, IC16.1, R136.2, R142.1
OUT31: C78.2, IC16.7, JP16.3, R139.1
OUT32: C81.2, IC17.1, R145.2, R151.1
OUT33: C83.2, IC17.7, JP17.3, R148.1
OUT34: C86.2, IC18.1, R154.2, R160.1
OUT35: C88.2, IC18.7, JP18.3, R157.1
OUT36: C91.2, IC19.1, R163.2, R169.1
OUT37: C93.2, IC19.7, JP19.3, R166.1
OUT38: C96.2, IC20.1, R172.2, R178.1
OUT39: C98.2, IC20.7, JP20.3, R175.1
OUT40: C101.2, IC21.1, R181.2, R187.1
OUT41: C103.2, IC21.7, JP21.3, R184.1
OUT42: C106.2, IC22.1, R190.2, R196.1
OUT43: C108.2, IC22.7, JP22.3, R193.1
OUT44: C111.2, IC23.1, R199.2, R205.1
OUT45: C113.2, IC23.7, JP23.3, R202.1
OUT46: C116.2, IC24.1, R208.2, R214.1
OUT47: C118.2, IC24.7, JP24.3, R211.1
OUT48: C121.2, IC25.1, R217.2, R223.1
OUT49: C123.2, IC25.7, JP25.3, R220.1
OUT50: C126.2, IC26.1, R226.2, R232.1
OUT51: C128.2, IC26.7, JP26.3, R229.1
OUT52: C131.2, IC27.1, R235.2, R241.1
OUT53: C133.2, IC27.7, JP27.3, R238.1
OUT54: C136.2, IC28.1, R244.2, R250.1
OUT55: C138.2, IC28.7, JP28.3, R247.1
OUT56: C141.2, IC29.1, R253.2, R259.1
OUT57: C143.2, IC29.7, JP29.3, R256.1
OUT58: C146.2, IC30.1, R262.2, R268.1
OUT59: C148.2, IC30.7, JP30.3, R265.1
OUT60: C151.2, IC31.1, R271.2, R277.1
OUT61: C153.2, IC31.7, JP31.3, R274.1
OUT62: C156.2, IC32.1, R280.2, R286.1
OUT63: C158.2, IC32.7, JP32.3, R283.1
OUT64: C161.2, IC33.1, R289.2, R295.1
OUT65: C163.2, IC33.7, JP33.3, R292.1
OUT66: C166.2, IC34.1, R298.2, R304.1
OUT67: C168.2, IC34.7, JP34.3, R301.1
OUT68: C171.2, IC35.1, R307.2, R313.1
OUT69: C173.2, IC35.7, JP35.3, R310.1
OUT70: C176.2, IC36.1, R316.2, R322.1
OUT71: C178.2, IC36.7, JP36.3, R319.1
OUT72: C181.2, IC37.1, R325.2, R331.1
OUT73: C183.2, IC37.7, JP37.3, R328.1
OUT74: C186.2, IC38.1, R334.2, R340.1
OUT75: C188.2, IC38.7, JP38.3, R337.1
OUT76: C191.2, IC39.1, R343.2, R349.1
OUT77: C193.2, IC39.7, JP39.3, R346.1
OUT78: C196.2, IC40.1, R352.2, R358.1
OUT79: C198.2, IC40.7, JP40.3, R355.1
OUT80: C201.2, IC41.1, R361.2, R367.1
OUT81: C203.2, IC41.7, JP41.3, R364.1
OUT82: C206.2, IC42.1, R370.2, R376.1
OUT83: C208.2, IC42.7, JP42.3, R373.1
OUT84: C211.2, IC43.1, R379.2, R385.1
OUT85: C213.2, IC43.7, JP43.3, R382.1
OUT86: C216.2, IC44.1, R388.2, R394.1
OUT87: C218.2, IC44.7, JP44.3, R391.1
OUT88: C221.2, IC45.1, R397.2, R403.1
OUT89: C223.2, IC45.7, JP45.3, R400.1
OUT90: C226.2, IC46.1, R406.2, R412.1
OUT91: C228.2, IC46.7, JP46.3, R409.1
OUT92: C231.2, IC47.1, R415.2, R421.1
OUT93: C233.2, IC47.7, JP47.3, R418.1
OUT94: C236.2, IC48.1, R424.2, R430.1
OUT95: C238.2, IC48.7, JP48.3, R427.1
OUT96: C241.2, IC49.1, R433.2, R439.1
OUT97: C243.2, IC49.7, JP49.3, R436.1
OUT98: C246.2, IC50.1, R442.2, R448.1
OUT99: C248.2, IC50.7, JP50.3, R445.1
OUT100: C251.2, IC51.1, R451.2, R457.1
OUT101: C253.2, IC51.7, JP51.3, R454.1
OUT102: C256.2, IC52.1, R460.2, R466.1
OUT103: C258.2, IC52.7, JP52.3, R463.1
OUT104: C261.2, IC53.1, R469.2, R475.1
OUT105: C263.2, IC53.7, JP53.3, R472.1
OUT106: C266.2, IC54.1, R478.2, R484.1
OUT107: C268.2, IC54.7, JP54.3, R481.1
OUT108: C271.2, IC55.1, R487.2, R493.1
OUT109: C273.2, IC55.7, JP55.3, R490.1
OUT110: C276.2, IC56.1, R496.2, R502.1
OUT111: C278.2, IC56.7, JP56.3, R499.1
OUT112: C281.2, IC57.1, R505.2, R511.1
OUT113: C283.2, IC57.7, JP57.3, R508.1
OUT114: C286.2, IC58.1, R514.2, R520.1
OUT115: C288.2, IC58.7, JP58.3, R517.1
OUT116: C291.2, IC59.1, R523.2, R529.1
OUT117: C293.2, IC59.7, JP59.3, R526.1
OUT118: C296.2, IC60.1, R532.2, R538.1
OUT119: C298.2, IC60.7, JP60.3, R535.1
OUT120: C301.2, IC61.1, R541.2, R547.1
OUT121: C303.2, IC61.7, JP61.3, R544.1
OUT122: C306.2, IC62.1, R550.2, R556.1
OUT123: C308.2, IC62.7, JP62.3, R553.1
OUT124: C311.2, IC63.1, R559.2, R565.1
OUT125: C313.2, IC63.7, JP63.3, R562.1
OUT126: C316.2, IC64.1, R568.2, R574.1
OUT127: C318.2, IC64.7, JP64.3, R571.1
VCC: C2.1, IC1.8, JP1.1, R8.1, R9.1
VCC1: C7.1, IC2.8, JP2.1, R17.1, R18.1
VCC2: C12.1, IC3.8, JP3.1, R26.1, R27.1
VCC3: C17.1, IC4.8, JP4.1, R35.1, R36.1
VCC4: C22.1, IC5.8, JP5.1, R44.1, R45.1
VCC5: C27.1, IC6.8, JP6.1, R53.1, R54.1
VCC6: C32.1, IC7.8, JP7.1, R62.1, R63.1
VCC7: C37.1, IC8.8, JP8.1, R71.1, R72.1
VCC8: C42.1, IC9.8, JP9.1, R80.1, R81.1
VCC9: C47.1, IC10.8, JP10.1, R89.1, R90.1
VCC10: C52.1, IC11.8, JP11.1, R98.1, R99.1
VCC11: C57.1, IC12.8, JP12.1, R107.1, R108.1
VCC12: C62.1, IC13.8, JP13.1, R116.1, R117.1
VCC13: C67.1, IC14.8, JP14.1, R125.1, R126.1
VCC14: C72.1, IC15.8, JP15.1, R134.1, R135.1
VCC15: C77.1, IC16.8, JP16.1, R143.1, R144.1
VCC16: C82.1, IC17.8, JP17.1, R152.1, R153.1
VCC17: C87.1, IC18.8, JP18.1, R161.1, R162.1
VCC18: C92.1, IC19.8, JP19.1, R170.1, R171.1
VCC19: C97.1, IC20.8, JP20.1, R179.1, R180.1
VCC20: C102.1, IC21.8, JP21.1, R188.1, R189.1
VCC21: C107.1, IC22.8, JP22.1, R197.1, R198.1
VCC22: C112.1, IC23.8, JP23.1, R206.1, R207.1
VCC23: C117.1, IC24.8, JP24.1, R215.1, R216.1
VCC24: C122.1, IC25.8, JP25.1, R224.1, R225.1
VCC25: C127.1, IC26.8, JP26.1, R233.1, R234.1
VCC26: C132.1, IC27.8, JP27.1, R242.1, R243.1
VCC27: C137.1, IC28.8, JP28.1, R251.1, R252.1
VCC28: C142.1, IC29.8, JP29.1, R260.1, R261.1
VCC29: C147.1, IC30.8, JP30.1, R269.1, R270.1
VCC30: C152.1, IC31.8, JP31.1, R278.1, R279.1
VCC31: C157.1, IC32.8, JP32.1, R287.1, R288.1
VCC32: C162.1, IC33.8, JP33.1, R296.1, R297.1
VCC33: C167.1, IC34.8, JP34.1, R305.1, R306.1
VCC34: C172.1, IC35.8, JP35.1, R314.1, R315.1
VCC35: C177.1, IC36.8, JP36.1, R323.1, R324.1
VCC36: C182.1, IC37.8, JP37.1, R332.1, R333.1
VCC37: C187.1, IC38.8, JP38.1, R341.1, R342.1
VCC38: C192.1, IC39.8, JP39.1, R350.1, R351.1
VCC39: C197.1, IC40.8, JP40.1, R359.1, R360.1
VCC40: C202.1, IC41.8, JP41.1, R368.1, R369.1
VCC41: C207.1, IC42.8, JP42.1, R377.1, R378.1
VCC42: C212.1, IC43.8, JP43.1, R386.1, R387.1
VCC43: C217.1, IC44.8, JP44.1, R395.1, R396.1
VCC44: C222.1, IC45.8, JP45.1, R404.1, R405.1
VCC45: C227.1, IC46.8, JP46.1, R413.1, R414.1
VCC46: C232.1, IC47.8, JP47.1, R422.1, R423.1
VCC47: C237.1, IC48.8, JP48.1, R431.1, R432.1
VCC48: C242.1, IC49.8, JP49.1, R440.1, R441.1
VCC49: C247.1, IC50.8, JP50.1, R449.1, R450.1
VCC50: C252.1, IC51.8, JP51.1, R458.1, R459.1
VCC51: C257.1, IC52.8, JP52.1, R467.1, R468.1
VCC52: C262.1, IC53.8, JP53.1, R476.1, R477.1
VCC53: C267.1, IC54.8, JP54.1, R485.1, R486.1
VCC54: C272.1, IC55.8, JP55.1, R494.1, R495.1
VCC55: C277.1, IC56.8, JP56.1, R503.1, R504.1
VCC56: C282.1, IC57.8, JP57.1, R512.1, R513.1
VCC57: C287.1, IC58.8, JP58.1, R521.1, R522.1
VCC58: C292.1, IC59.8, JP59.1, R530.1, R531.1
VCC59: C297.1, IC60.8, JP60.1, R539.1, R540.1
VCC60: C302.1, IC61.8, JP61.1, R548.1, R549.1
VCC61: C307.1, IC62.8, JP62.1, R557.1, R558.1
VCC62: C312.1, IC63.8, JP63.1, R566.1, R567.1
VCC63: C317.1, IC64.8, JP64.1, R575.1, R576.1

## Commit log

2015-05-05 Adding hardware files, updating README
2015-05-05 Adding version number to schematic
2015-12-10 created panel v16

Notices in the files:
parts and their libraries:
SparkFun-Aesthetics: Licensing: CC v3.0 Share-Alike You are welcome to use this library for commercial purposes.
SparkFun-Retired: Licensing:Creative Commons ShareAlike 4.0 International - https://creativecommons.org/licenses/by-sa/4.0
